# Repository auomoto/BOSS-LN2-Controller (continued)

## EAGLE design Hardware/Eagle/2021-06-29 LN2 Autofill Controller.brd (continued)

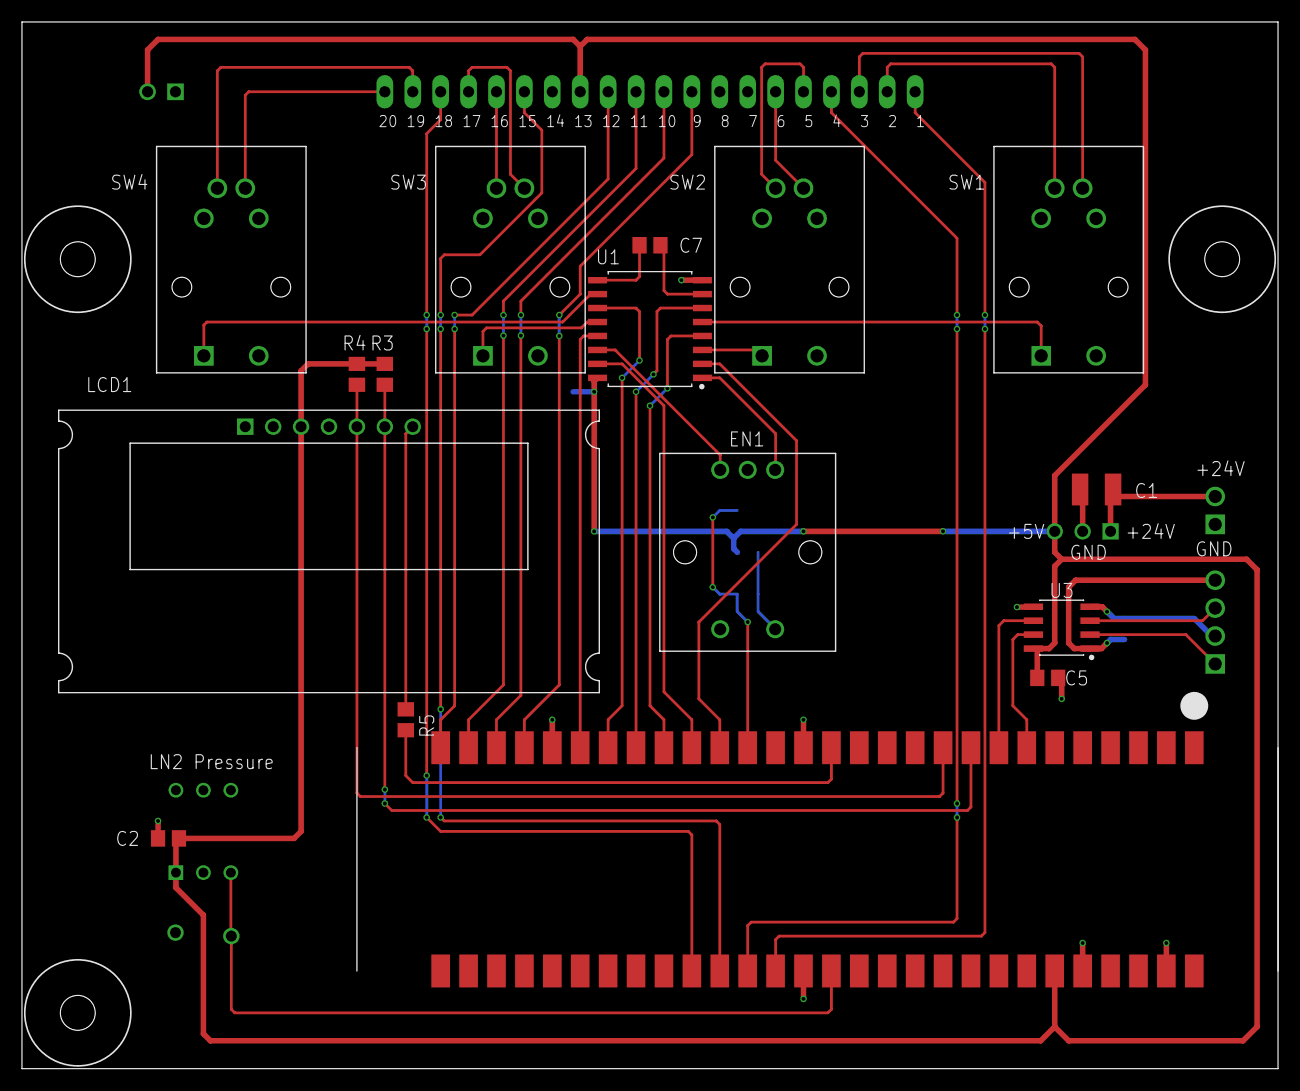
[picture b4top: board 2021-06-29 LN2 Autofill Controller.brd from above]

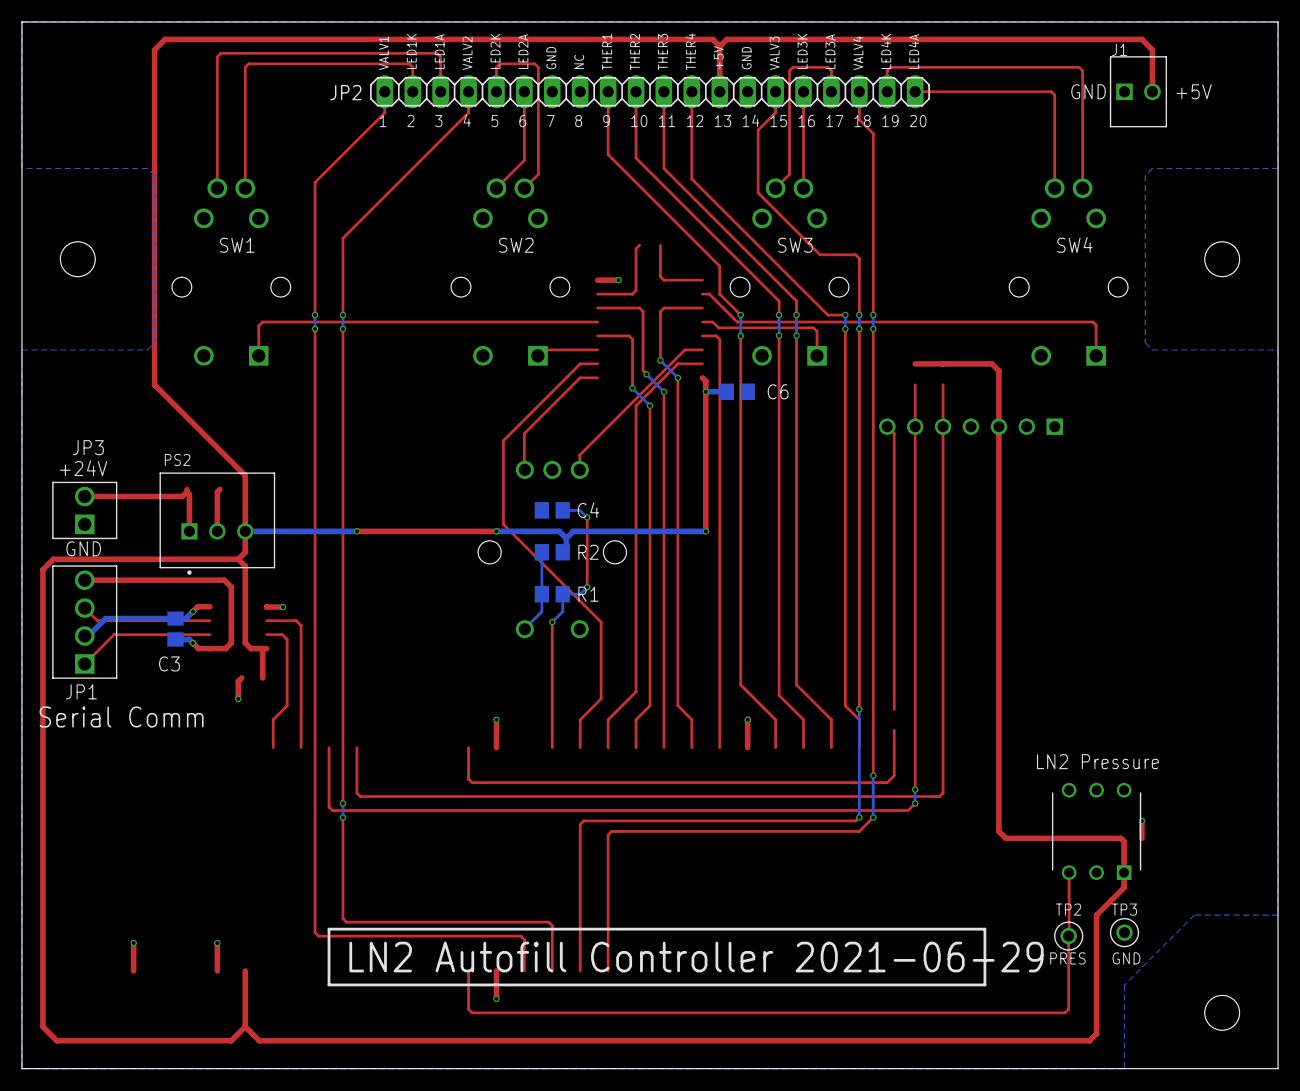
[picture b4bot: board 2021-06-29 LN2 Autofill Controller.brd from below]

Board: 2 copper layers, 114.3 x 95.2 mm, 29 parts (13 on the bottom side), 46 nets.

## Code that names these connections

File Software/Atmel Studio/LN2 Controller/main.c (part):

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
VALVn is the electronics schematic net name.

VALV1 is on pin PC7 (Blue dewar vent)
VALV2 is on pin PC6 (Red dewar vent)
VALV3 is on pin PC5 (Buffer dewar vent)
VALV4 is on pin PC4 (Supply input valve)
----------------------------------------------------------------------*/
void init_Valves(void)
{
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The on-board pushbutton switch on the Curiosity Nano has an external
pullup on it but no debouncing.

PB2 is SW1 Blue dewar vent
PB3 is SW2 Red dewar vent
PB0 is SW3 Buffer dewar vent
PB1 is SW4 Buffer dewar supply inlet
PF6 is the Curiosity Nano on-board pushbutton
----------------------------------------------------------------------*/
void init_Switches()
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The rotary encoder channels A and B go through the debouncer IC.
The pushbutton on the rotary encoder has a pullup and an RC debouncer.

PC3 is ENCA encoder A signal
PC2 is ENCB encoder B signal (does not cause an interrupt)
PC1 is PUSH encoder pushbutton

WAIT: TRIGGER ON RISING VALUES INSTEAD? AFTER 4 MS THIS WILL SETTLE
INTO A DETENT. TRIGGERING ON FALLING VALUES IS BETWEEN DETENTS
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{
	
	// Rotary Encoder
	PORTC.PIN3CTRL = PORT_PULLUPEN_bm | PORT_ISC_FALLING_gc;	// ENCA
	PORTC.PIN2CTRL = PORT_PULLUPEN_bm;							// ENCB
	PORTC.PIN1CTRL = PORT_PULLUPEN_bm | PORT_ISC_FALLING_gc;	// PUSH

}

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installed as well. Three pins (0, 1, and 2) have interrupts enabled.

PINn_bm assignments:
Thermistor 1 is on pin PE0 (Blue vent thermistor)
Thermistor 2 is on pin PE1 (Red vent thermistor)
Thermistor 3 is on pin PE2 (Buffer vent thermistor)
Thermistor 4 is on pin PE3 (No thermistor assigned)
----------------------------------------------------------------------*/
void init_Thermistors(void)
{
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//	VREF.CTRLA |= VREF_ADC0REFSEL_2V5_gc;	// Use 2.5V
	ADC0_CTRLC |= ADC_REFSEL_INTREF_gc;		// Use internal vref
	ADC0_CTRLC |= ADC_SAMPCAP_bm;			// Reduce sampling capacitance
	ADC0_MUXPOS = ADC_MUXPOS_AIN0_gc;		// PD0 pin feeds ADC
	ADC0.CTRLA |= ADC_ENABLE_bm;			// Enable ADC
	ADC0_COMMAND |= ADC_STCONV_bm;			// Start ADC conversion
	while (ADC0_COMMAND & ADC_STCONV_bm) {
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void init_Serial(void)
{

	// USART0 PA0 is TxD, PA1 is RxD, Default pin position
	PORTA.OUTSET = PIN0_bm;
	PORTA.DIRSET = PIN0_bm;
	USART0.BAUD = (uint16_t) USART_BAUD_RATE(9600);
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
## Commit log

2020-10-28 Initial Load
    Transferred from old GIT directory
2020-11-27 Updated library to put Curiosity Nano in 3D
2020-11-28 Added 6-pin RJ11 breakout board
    The 4-pin versions are less common and out of stock at Digikey (2020-11-28) while the 6-pin versions are OK
2020-11-29 Switched to a right angle connector on the RJ11 breakout
2020-11-30 Swapped 5VDC convert to stand-up version
2020-11-30 Removed top & bottom copper pours
2020-11-30 Removed bottom polygon (missed some before)
2020-11-30 Start rewiring
2020-11-30 Rerouted controller board, putting most traces on the top
2021-01-05 Save minor changes?
2021-01-24 Removed Eagle backups for gitignore
2021-02-10 Examined RJ11 connectors (no changes)
2021-02-19 Re-pinned the serial connector, changed track widths
2021-02-20 Made copies of the RJ11 breakout and ? on LN2 board
2021-02-22 Added gate resistor and re-routed connector board
2021-07-24 FInal check before ordering
2021-08-19 Brought in test code developed in a different directory
2021-08-26 Revised for new LN2 controller board
2021-08-28 Added USART routines
2021-08-28 Simplified a bit
2021-08-31 Minor mods, added OLEDTIMEOUT
2021-09-01 Minor edits
2021-09-12 Fast update on pressure display (not tested)
2021-09-13 Pressure pressure display update
    Turn off the pressure display if the number hasn't changed
2021-09-20 Added overfill time
2021-09-24 Set buffer overfill time to 15 sec
    We watched the fill in the lab to get this number
2021-11-10 Fixed power-on sup valve open problem
2022-01-20 Added solid model
2022-03-04 Added supply button safety feature
2022-05-24 Modified usart.c for new specMech format
2022-05-27 Reformatted serial report, removed 2s cable msg
2022-05-30 Diagnostic changes; no performance impact
2022-05-31 Reformat report line
2022-06-14 Added TCB2 oscillator signal for debouncer
    Need to put in a wire from PC0 to the right-hand pad near the debouncer
2022-07-15 Created no-debouncer version
2022-07-17 Worked out bugs on no-debouncer version
2023-01-24 Updates?
2023-09-14 LN2 autofill update
